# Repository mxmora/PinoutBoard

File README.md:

# PinoutBoard
simple breakout board

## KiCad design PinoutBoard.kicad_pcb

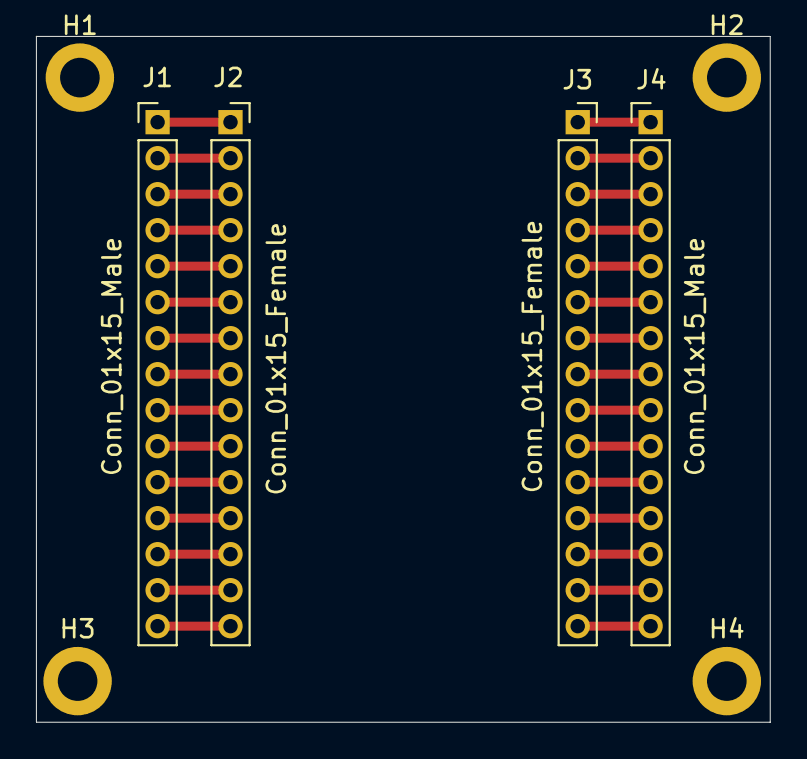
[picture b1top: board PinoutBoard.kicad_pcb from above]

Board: 2 copper layers, 40.8 x 38.1 mm, 8 parts (0 on the bottom side), 31 nets.

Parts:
H1, H2, H3, H4: MountingHole_Pad; MountingHole_2.2mm_M2_DIN965_Pad
J1, J4: Conn_01x15_Male; PinHeader_1x15_P2.00mm_Vertical
J2, J3: Conn_01x15_Female; PinSocket_1x15_P2.00mm_Vertical

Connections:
GND: H1.1, H2.1, H3.1, H4.1
unnamed: J1.1, J2.1
unnamed: J1.2, J2.2
unnamed: J1.3, J2.3
unnamed: J1.4, J2.4
unnamed: J1.5, J2.5
unnamed: J1.6, J2.6
unnamed: J1.7, J2.7
unnamed: J1.8, J2.8
unnamed: J1.9, J2.9
unnamed: J1.10, J2.10
unnamed: J1.11, J2.11
unnamed: J1.12, J2.12
unnamed: J1.13, J2.13
unnamed: J1.14, J2.14
unnamed: J1.15, J2.15
unnamed: J3.1, J4.1
unnamed: J3.2, J4.2
unnamed: J3.3, J4.3
unnamed: J3.4, J4.4
unnamed: J3.5, J4.5
unnamed: J3.6, J4.6
unnamed: J3.7, J4.7
unnamed: J3.8, J4.8
unnamed: J3.9, J4.9
unnamed: J3.10, J4.10
unnamed: J3.11, J4.11
unnamed: J3.12, J4.12
unnamed: J3.13, J4.13
unnamed: J3.14, J4.14
unnamed: J3.15, J4.15
